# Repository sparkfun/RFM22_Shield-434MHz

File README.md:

SparkFun RFM22 Shield - 434MHz
========================================

[*SparkFun RFM22 Shield - 434MHz (DEV-11018)*](https://www.sparkfun.com/products/11018)

The RFM22 Shield connects the RFM22 module to the appropriate lines on the Arduino. 
By using the RF22 Library, you can send and receive messages via standard 4-wire SPI. 
The library includes command structures for setting up anything from simple non-addressed point-to-point communication to fully addressed networks of clients and routers. 
The shield also provides a through-hole antenna connection for hooking up a basic wire antenna.

Repository Contents
-------------------

* **/Firmware** - Example code 
* **/Hardware** - Eagle design files (.brd, .sch)
* **/Libraries** - Libraries for use with the <PRODUCT NAME>
* **/Production** - Production panel files (.brd)

Documentation
--------------
* **[Library](https://github.com/sparkfun/SparkFun_RadioHead_Arduino_Library)** - Arduino library for the RFM22 Shield.
* **[Hookup Guide](https://www.sparkfun.com/tutorials/381)** - Basic hookup guide for the RFM22 Shield.
* **[SparkFun Fritzing repo](https://github.com/sparkfun/Fritzing_Parts)** - Fritzing diagrams for SparkFun products.
* **[SparkFun 3D Model repo](https://github.com/sparkfun/3D_Models)** - 3D models of SparkFun products. 

License Information
-------------------
This product is _**open source**_! 

The **hardware** is released under [Creative Commons ShareAlike 4.0 International](https://creativecommons.org/licenses/by-sa/4.0/).

Please use, reuse, and modify these files as you see fit. Please maintain attribution to SparkFun Electronics and release anything derivative under the same license.

Distributed as-is; no warranty is given.

- Your friends at SparkFun.

_The library is the SparkFun fork of the RadioHead library by Mike McCauley. The original library can be found here: http://www.airspayce.com/mikem/arduino/RadioHead/_

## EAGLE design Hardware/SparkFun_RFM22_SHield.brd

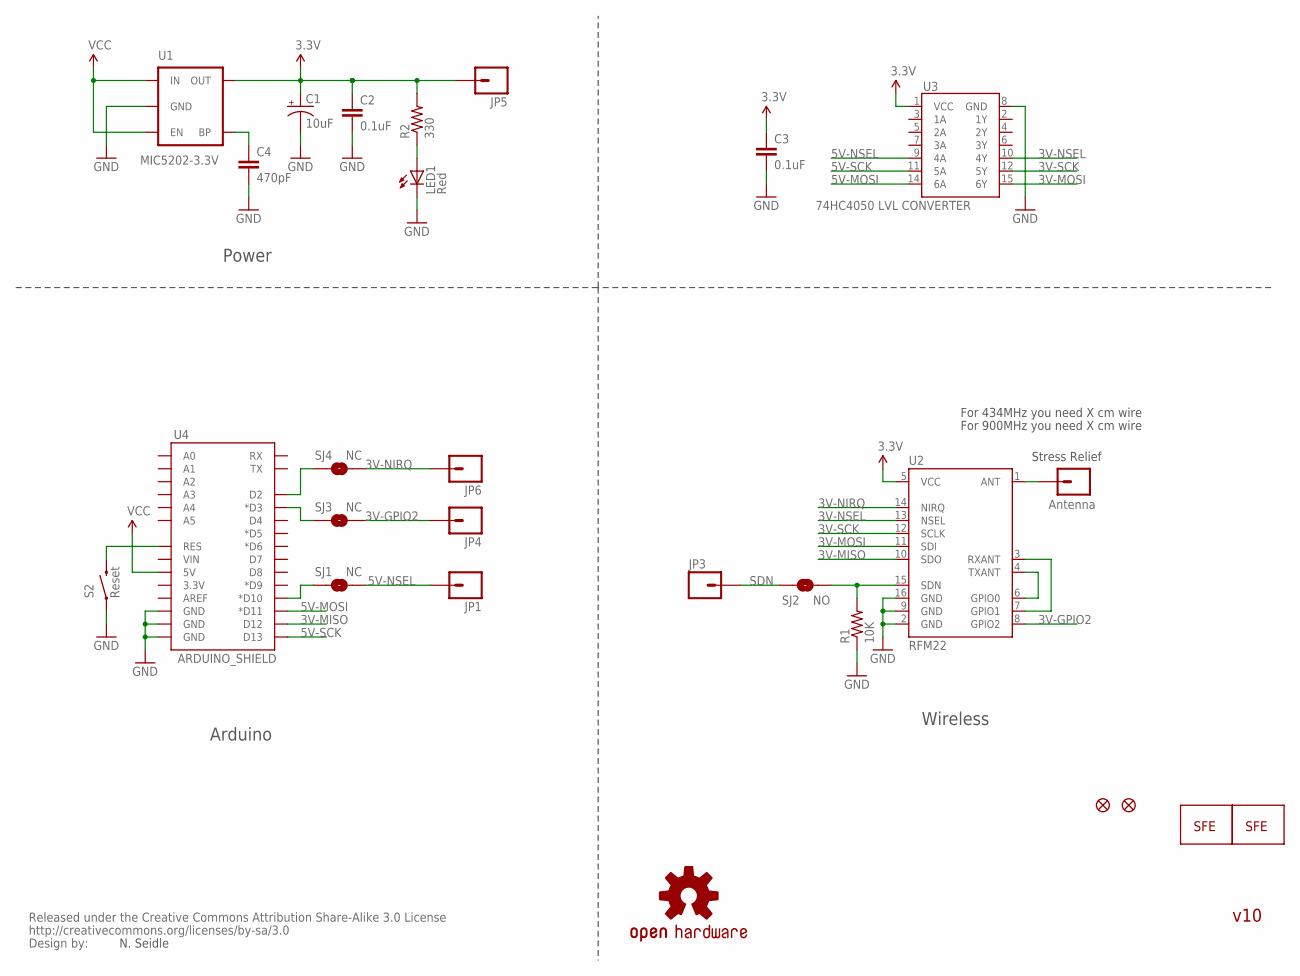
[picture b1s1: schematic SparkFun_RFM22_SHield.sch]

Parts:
C1: 10uF; EIA3216
C2, C3: 0.1uF; 0402-CAP
C4: 470pF; 0402-CAP
JP1, JP3, JP4, JP5, JP6: M01PTH; 1X01
JP2: Antenna; 1X01
JP7, JP8: FIDUCIALUFIDUCIAL; MICRO-FIDUCIAL
LED1: Red; LED-0603
R1: 10K; 0402-RES
R2: 330; 0402-RES
S2: Reset; TACTILE_SWITCH_SMD
SJ1, SJ3, SJ4: NC; SJ_2S-TRACE
SJ2: NO; SJ_2S-NO
U1: MIC5202-3.3V; SOT23-5
U2: RFM22; RFM22-XXX-S2
U3: 74HC4050 LVL CONVERTER; SO016
U4: ARDUINO_SHIELD; DUEMILANOVE_SHIELD_NOHOLES
U$1: OSHW-LOGOS; OSHW-LOGO-S
U$3: CREATIVE_COMMONS
U$7, U$8: LOGO-SFENEW; SFE-NEW-WEBLOGO

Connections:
3.3V: C1.A (+), C2.1, C3.1, JP5.1, R2.2, U1.5 (OUT), U2.5 (VCC), U3.1 (VCC)
3V-GPIO2: JP4.1, SJ3.2, U2.8 (GPIO2)
3V-MISO: U2.10 (SDO), U4.D12
3V-MOSI: U2.11 (SDI), U3.15 (6Y)
3V-NIRQ: JP6.1, SJ4.2, U2.14 (NIRQ)
3V-NSEL: U2.13 (NSEL), U3.10 (4Y)
3V-SCK: U2.12 (SCLK), U3.12 (5Y)
5V-MOSI: U3.14 (6A), U4.D11 (*D11)
5V-NSEL: JP1.1, SJ1.2, U3.9 (4A)
5V-SCK: U3.11 (5A), U4.D13
ARST: S2.3 (2), U4.RES
GND: C1.C (-), C2.2, C3.2, C4.2, LED1.C, R1.1, S2.1, U1.2 (GND), U2.2 (GND), U2.9 (GND), U2.16 (GND), U3.8 (GND), U4.GND@0 (GND), U4.GND@1 (GND), U4.GND@2 (GND)
unnamed: JP2.1, U2.1 (ANT)
unnamed: SJ1.1, U4.D10 (*D10)
unnamed: U2.4 (TXANT), U2.6 (GPIO0)
unnamed: U2.3 (RXANT), U2.7 (GPIO1)
unnamed: SJ3.1, U4.D3 (*D3)
unnamed: LED1.A, R2.1
unnamed: SJ4.1, U4.D2
unnamed: C4.1, U1.4 (BP)
SDN: JP3.1, SJ2.1
SDN2: R1.2, SJ2.2, U2.15 (SDN)
VCC: U1.1 (IN), U1.3 (EN), U4.5V

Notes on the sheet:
N. Seidle
Power
Arduino
Stress Relief
For 434MHz you need X cm wire
For 900MHz you need X cm wire
Wireless
v10

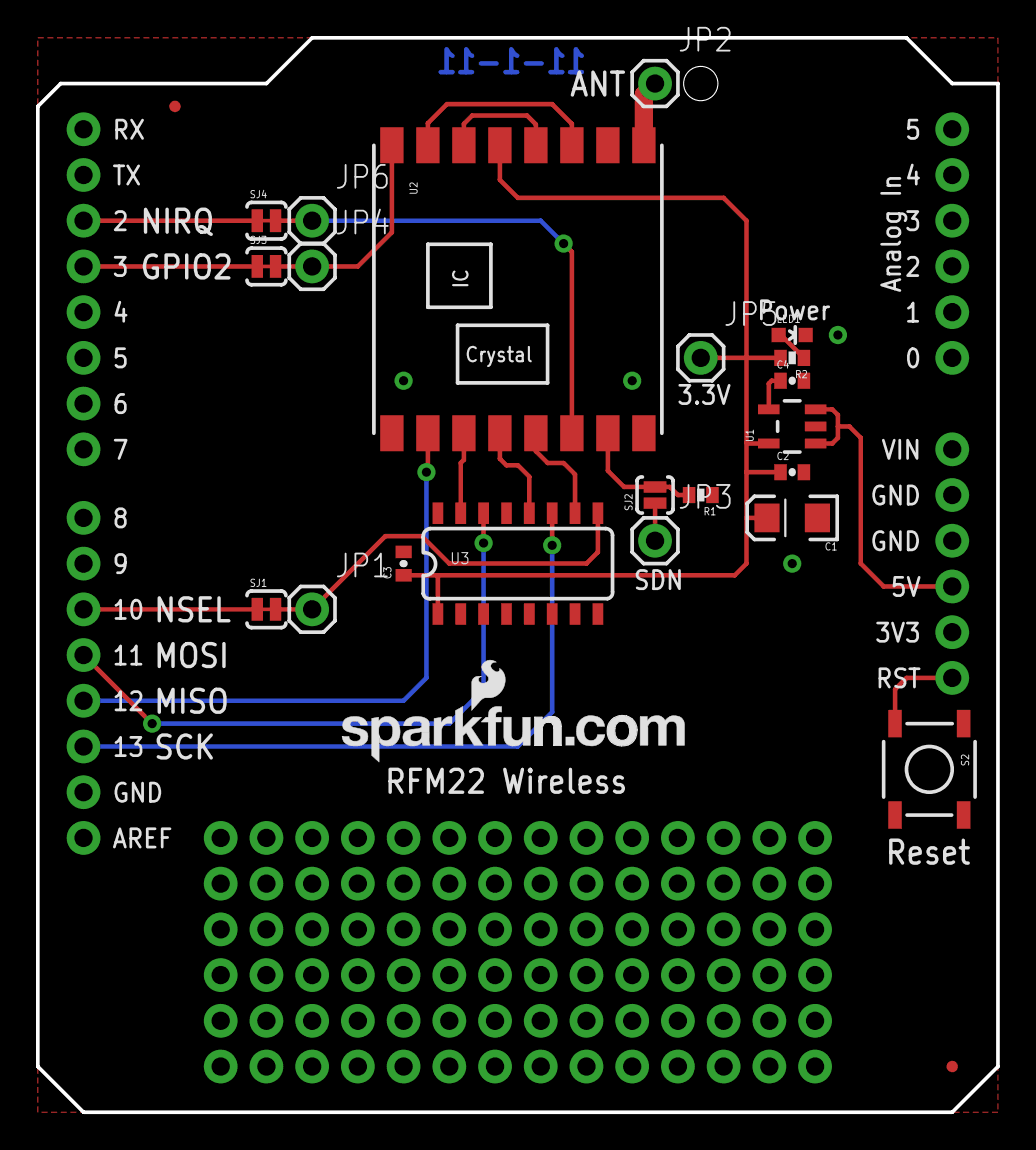
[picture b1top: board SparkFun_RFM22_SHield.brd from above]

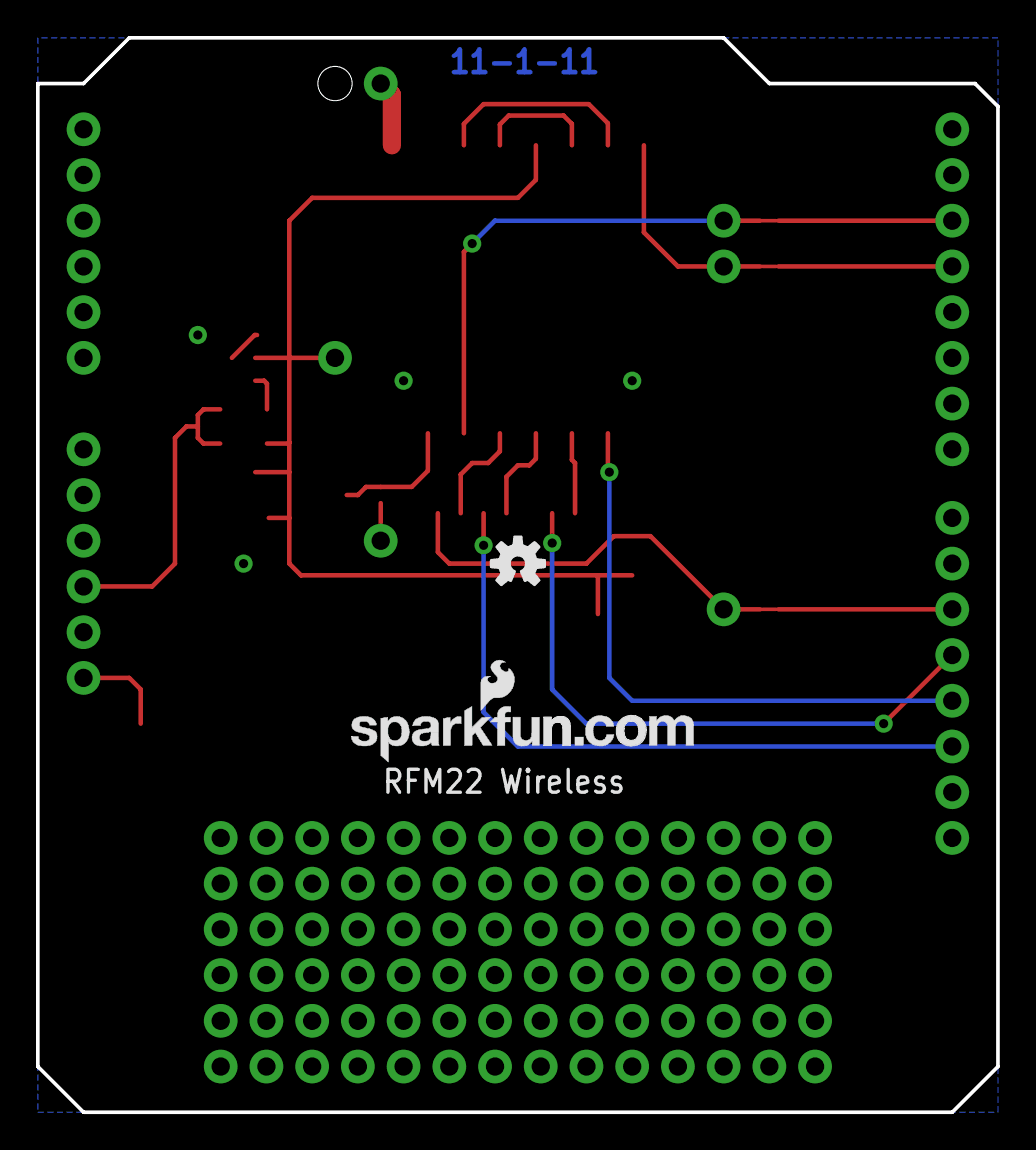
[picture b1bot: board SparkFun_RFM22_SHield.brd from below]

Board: 2 copper layers, 53.3 x 59.7 mm, 28 parts (2 on the bottom side), 23 nets.

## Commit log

2015-05-13 Adding example sketches, hardware files
2015-05-13 Updating README
2015-05-13 Squashed 'Libraries/Arduino/' content from commit b79a741
    git-subtree-dir: Libraries/Arduino
    git-subtree-split: b79a7412439733b9bf97c1cfd8eaaa227ad349ff
2015-05-13 Updating license to point towards library license

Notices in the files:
parts and their libraries:
SparkFun: Released under the Creative Commons Attribution Share-Alike 3.0 License
SparkFun: http://creativecommons.org/licenses/by-sa/3.0
